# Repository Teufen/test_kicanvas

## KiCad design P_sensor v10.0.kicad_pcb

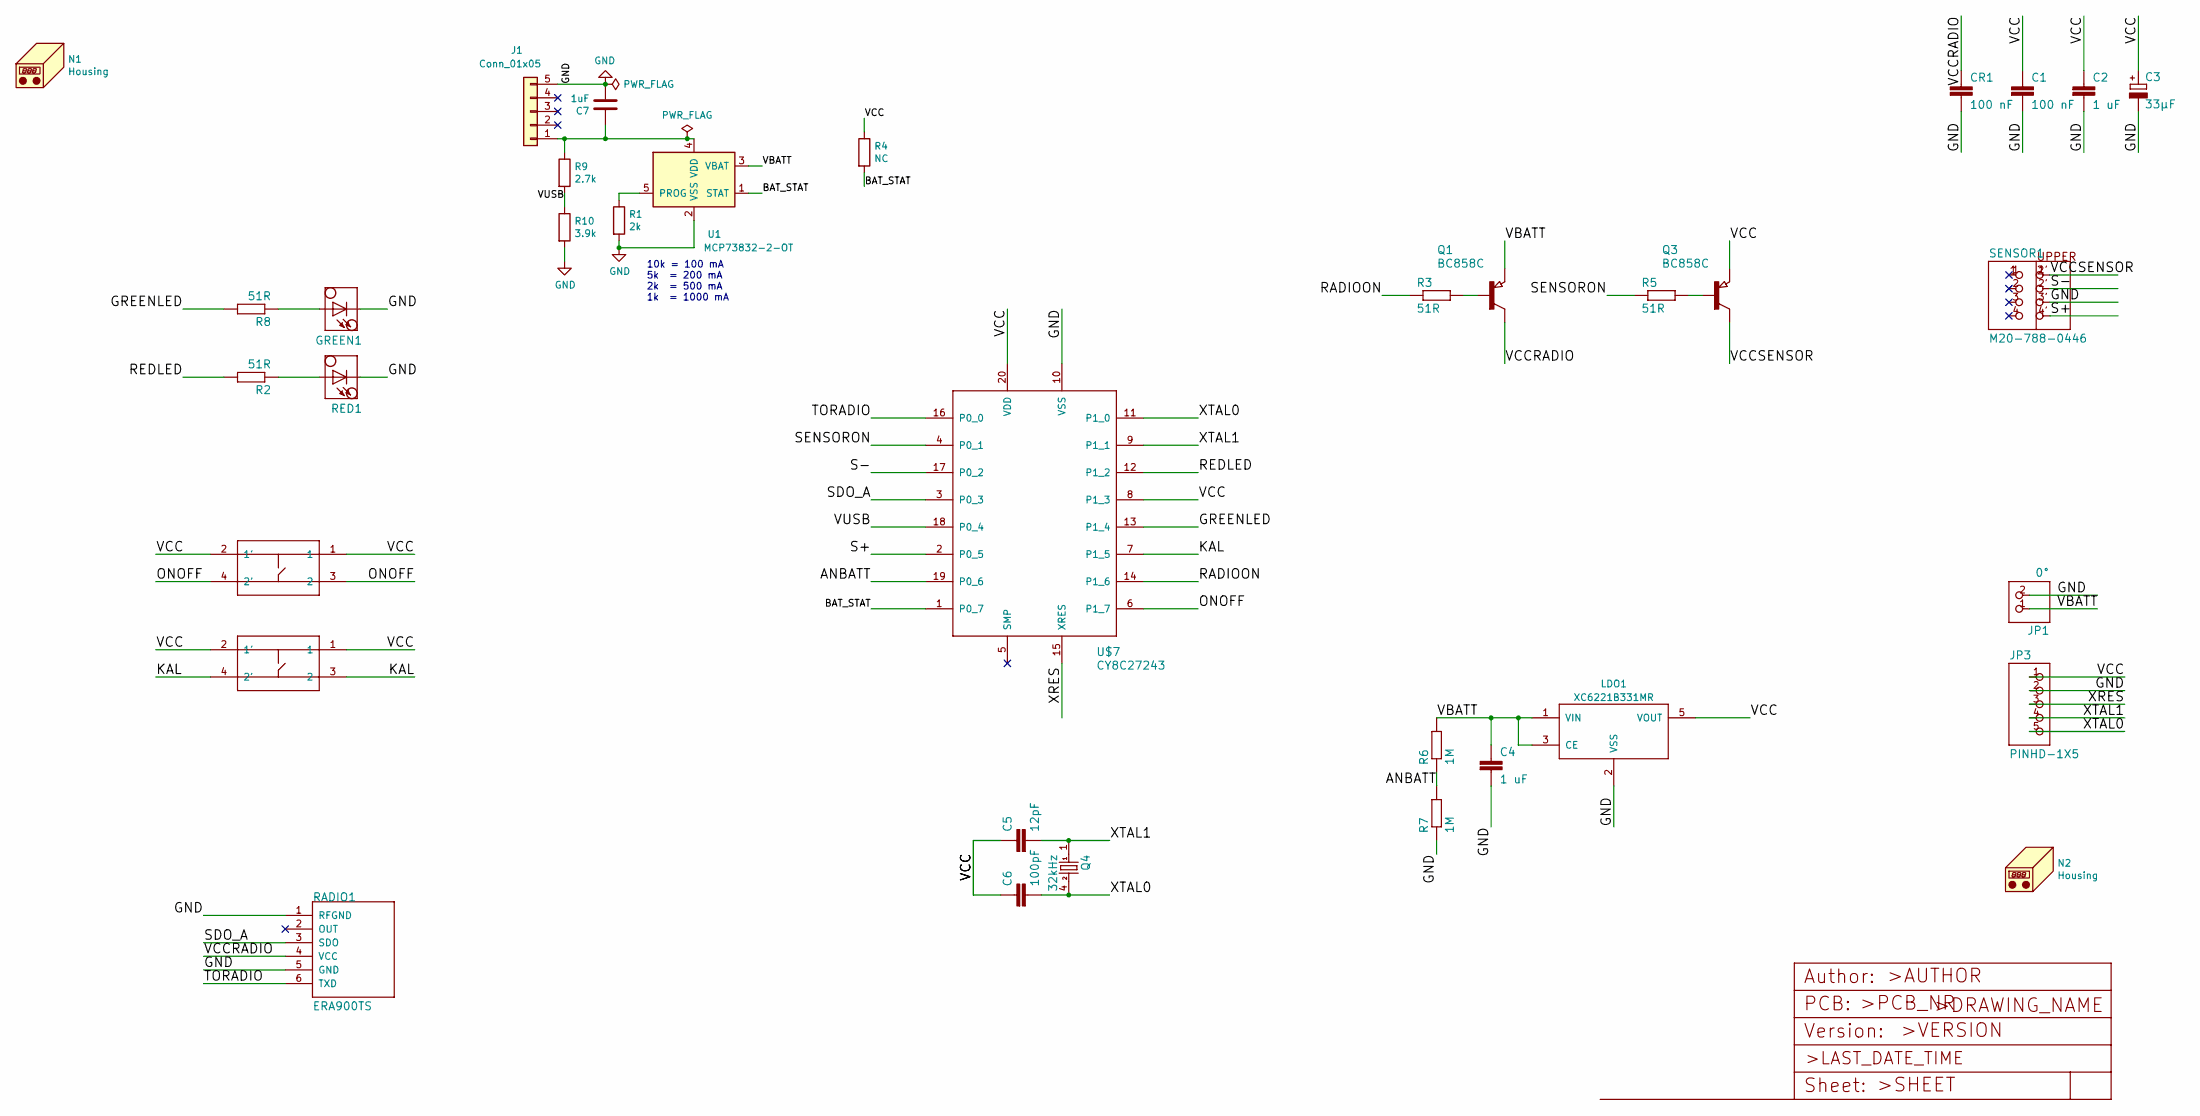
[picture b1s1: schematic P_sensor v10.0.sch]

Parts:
C1: 100 nF; C0603
C2, C4: 1 uF; C0603
C3: 33µF; SMC_C
C5: 12pF; C0603
C6: 100pF; C0603
C7: 1uF; C_0603_1608Metric; MPN GCJ188R71E105KA01D
CR1: 100 nF; C0603
GREEN1: KP-3216SGC_W_KSMJ01/06; CHIPLED_1206_WGUIDE
J1: Conn_01x05; Molex_USB_Mini_Horizontal_Through_Hole_54819-0519; MPN 54819-0519
JP1: 0°; 1X02
JP3: PINHD-1X5; 1X05
KAL1: 3ESL-XXX; 3E
LDO1: XC6221B331MR; SOT23-5L; MPN XC6221B331MR-G
N1: Housing; PCB_CENTER
N2: Housing; logopanimpex_700dpi
ONOFF1: 3ESL-XXX; 3E
Q1, Q3: BC858C; SOT23; MPN BC858C-7-F
Q4: 32kHz; 85SMX; MPN LFXTAL016178
R1: 2k; R_0603_1608Metric; MPN CRCW06032K00FKEA
R2, R3, R5, R8: 51R; M0805
R4: NC; R_0603_1608Metric
R6, R7: 1M; M0805
R9: 2.7k; R_0603_1608Metric; MPN RC0603FR-072K7L
R10: 3.9k; R_0603_1608Metric; MPN MCWR06X3901FTL
RADIO1: ERA900TS; ERAX00TS
RED1: KP-3216EC_W_KSMJ01/06; CHIPLED_1206_WGUIDE
SENSOR1: M20-788-0446; M20-7890446; MPN M20-7880446
U1: MCP73832-2-OT; SOT-23-5; MPN MCP73832T-2ACI/OT
U$7: CY8C27243; SSOP20; MPN CY8C27243-24PVXI

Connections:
/ANBATT: R6.1, R7.2, U$7.19 (P0_6)
/BAT_STAT: R4.2, U1.1 (STAT), U$7.1 (P0_7)
/GREENLED: R8.2, U$7.13 (P1_4)
/KAL: KAL1.3 (2), KAL1.4 (2'), U$7.7 (P1_5)
/ONOFF: ONOFF1.3 (2), ONOFF1.4 (2'), U$7.6 (P1_7)
/RADIOON: R3.1, U$7.14 (P1_6)
/REDLED: R2.2, U$7.12 (P1_2)
/S+: SENSOR1.4' (8), U$7.2 (P0_5)
/S-: SENSOR1.2' (4), U$7.17 (P0_2)
/SDO_A: RADIO1.3 (SDO), U$7.3 (P0_3)
/SENSORON: R5.1, U$7.4 (P0_1)
/TORADIO: RADIO1.6 (TXD), U$7.16 (P0_0)
/VBATT: C4.1, JP1.1, LDO1.1 (VIN), LDO1.3 (CE), Q1.2 (E), R6.2, U1.3 (VBAT)
/VCC: C1.1, C2.1, C3.+, C5.1, C6.1, JP3.1, KAL1.1, KAL1.2 (1'), LDO1.5 (VOUT), ONOFF1.1, ONOFF1.2 (1'), Q3.2 (E), R4.1, U$7.8 (P1_3), U$7.20 (VDD)
/VCCRADIO: CR1.1, Q1.3 (C), RADIO1.4 (VCC)
/VCCSENSOR: Q3.3 (C), SENSOR1.1' (2)
/VUSB: R9.2, R10.1, U$7.18 (P0_4)
/XRES: JP3.3, U$7.15 (XRES)
/XTAL0: C6.2, JP3.5, Q4.4 (2), U$7.11 (P1_0)
/XTAL1: C5.2, JP3.4, Q4.1, U$7.9 (P1_1)
GND: C1.2, C2.2, C3.-, C4.2, C7.2, CR1.2, GREEN1.C, J1.5, JP1.2, JP3.2, LDO1.2 (VSS), R1.2, R7.1, R10.2, RADIO1.1 (RFGND), RADIO1.5 (GND), RED1.C, SENSOR1.3' (6), U1.2 (VSS), U$7.10 (VSS)
unnamed: C7.1, J1.1, R9.1, U1.4 (VDD)
unnamed: GREEN1.A, R8.1
unnamed: Q1.1 (B), R3.2
unnamed: Q3.1 (B), R5.2
unnamed: R1.1, U1.5 (PROG)
unnamed: R2.1, RED1.A

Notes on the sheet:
10k = 100 mA 5k = 200 mA 2k = 500 mA 1k = 1000 mA

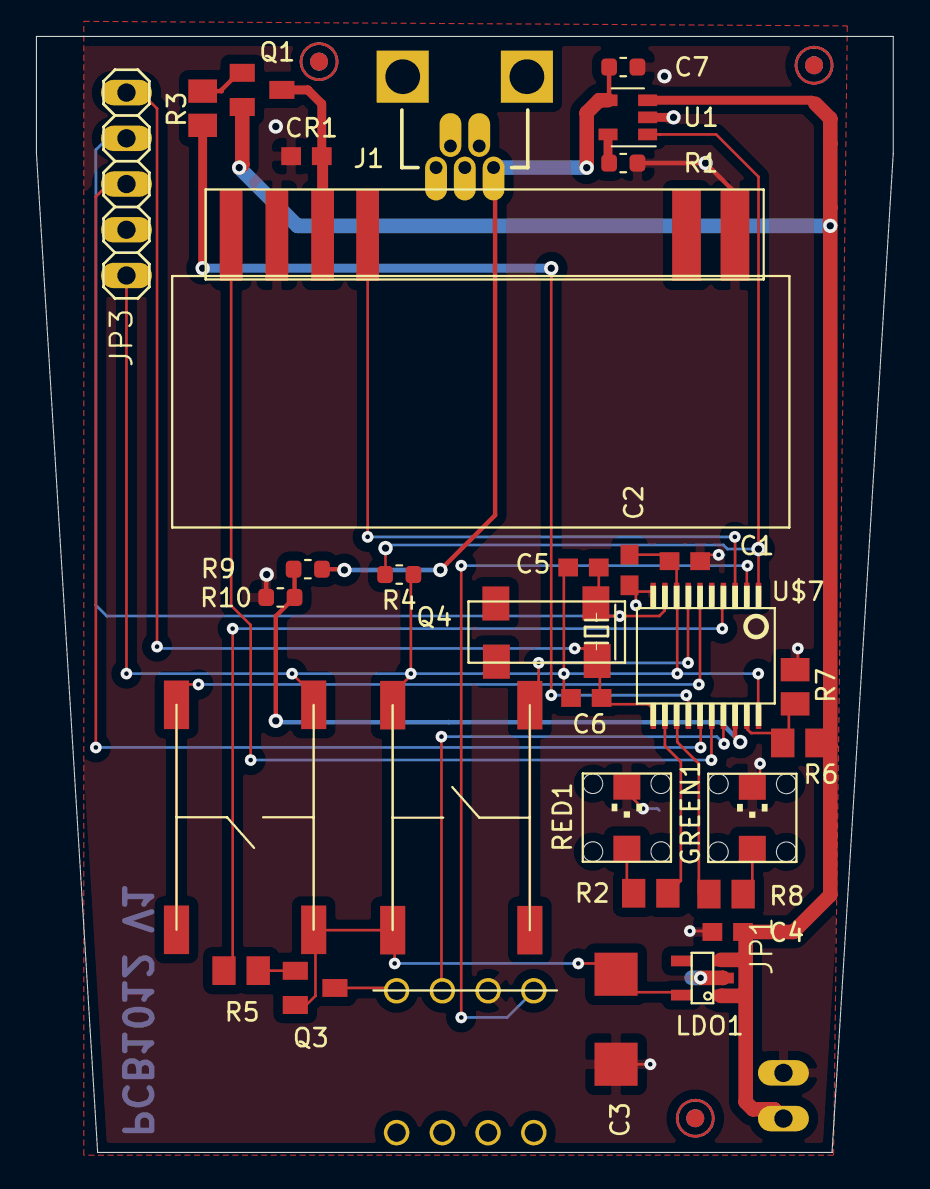
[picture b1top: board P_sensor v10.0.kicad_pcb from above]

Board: 16 copper layers, 47.6 x 62.0 mm, 39 parts (0 on the bottom side), 27 nets.

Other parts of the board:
U$1: DIM_SENSOR
U$3, U$4, U$5: FIDUCIAL_PAGE
